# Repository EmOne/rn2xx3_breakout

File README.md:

# rn2xx3_breakout

Feel free to make your own PCB.

Or

You can buy it at http://www.emone.co.th/product/rn2xx3-breakout/

#License
MIT License

Copyright (c) 2018 EmOne

Permission is hereby granted, free of charge, to any person obtaining a copy
of this software and associated documentation files (the "Software"), to deal
in the Software without restriction, including without limitation the rights
to use, copy, modify, merge, publish, distribute, sublicense, and/or sell
copies of the Software, and to permit persons to whom the Software is
furnished to do so, subject to the following conditions:

The above copyright notice and this permission notice shall be included in all
copies or substantial portions of the Software.

THE SOFTWARE IS PROVIDED "AS IS", WITHOUT WARRANTY OF ANY KIND, EXPRESS OR
IMPLIED, INCLUDING BUT NOT LIMITED TO THE WARRANTIES OF MERCHANTABILITY,
FITNESS FOR A PARTICULAR PURPOSE AND NONINFRINGEMENT. IN NO EVENT SHALL THE
AUTHORS OR COPYRIGHT HOLDERS BE LIABLE FOR ANY CLAIM, DAMAGES OR OTHER
LIABILITY, WHETHER IN AN ACTION OF CONTRACT, TORT OR OTHERWISE, ARISING FROM,
OUT OF OR IN CONNECTION WITH THE SOFTWARE OR THE USE OR OTHER DEALINGS IN THE
SOFTWARE.

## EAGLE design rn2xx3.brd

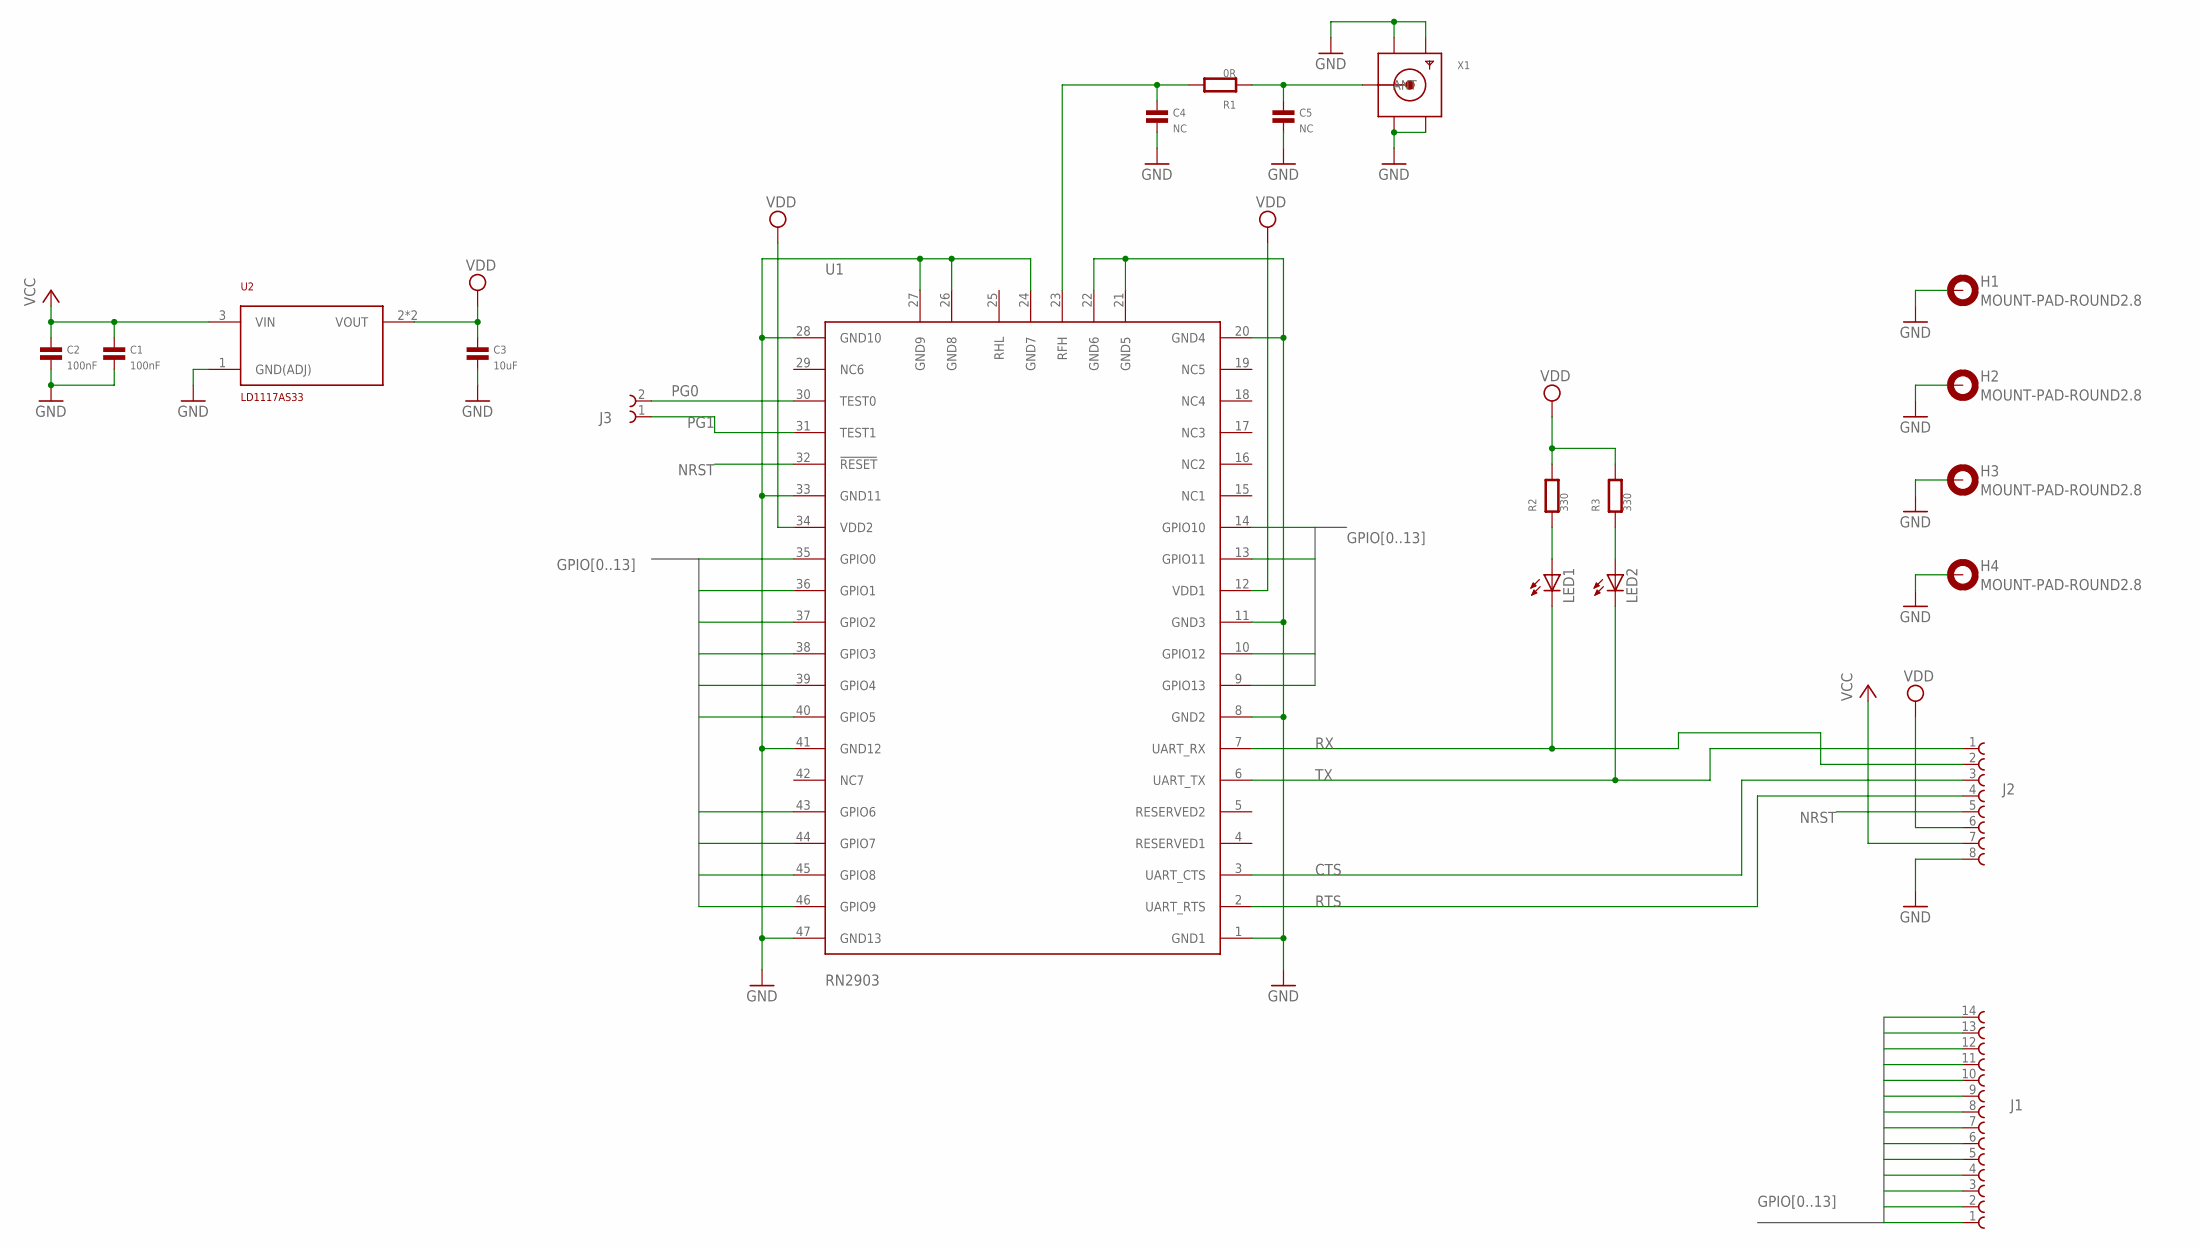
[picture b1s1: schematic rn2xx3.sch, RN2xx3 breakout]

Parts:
C1, C2: 100nF; 0603
C3: 10uF; 0603
C4, C5: NC; 0402
H1, H2, H3, H4: MOUNT-PAD-ROUND2.8; 2,8-PAD
J1: 61301411121
J2: 61300811021
J3: 61300211121
LED1, LED2: LED0603; 0603-LED
R1: 0R; 0402
R2, R3: 330; 0603
U1: RN2903; RN2483/RN2903
U2: LD1117AS33; SOT-223
X1: SMACONNECTOR_EDGE_UFL; SMA_EDGELAUNCH_UFL

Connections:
CTS: J2.3, U1.3 (UART_CTS)
GND: C1.2, C2.2, C3.2, C4.2, C5.2, H1.B2,8, H2.B2,8, H3.B2,8, H4.B2,8, J2.8, U1.1 (GND1), U1.8 (GND2), U1.11 (GND3), U1.20 (GND4), U1.21 (GND5), U1.22 (GND6), U1.24 (GND7), U1.26 (GND8), U1.27 (GND9), U1.28 (GND10), U1.33 (GND11), U1.41 (GND12), U1.47 (GND13), U2.1 (GND(ADJ)), X1.GND@1 (GND1), X1.GND@2 (GND2), X1.GND@3 (GND3), X1.GND@4 (GND4)
GPIO0: J1.1 (14), U1.35 (GPIO0)
GPIO1: J1.2 (13), U1.36 (GPIO1)
GPIO2: J1.3 (12), U1.37 (GPIO2)
GPIO3: J1.4 (11), U1.38 (GPIO3)
GPIO4: J1.5 (10), U1.39 (GPIO4)
GPIO5: J1.6 (9), U1.40 (GPIO5)
GPIO6: J1.7 (8), U1.43 (GPIO6)
GPIO7: J1.8 (7), U1.44 (GPIO7)
GPIO8: J1.9 (6), U1.45 (GPIO8)
GPIO9: J1.10 (5), U1.46 (GPIO9)
GPIO10: J1.11 (4), U1.14 (GPIO10)
GPIO11: J1.12 (3), U1.13 (GPIO11)
GPIO12: J1.13 (2), U1.10 (GPIO12)
GPIO13: J1.14 (1), U1.9 (GPIO13)
unnamed: C4.1, R1.2, U1.23 (RFH)
unnamed: C5.1, R1.1, X1.P (ANT)
unnamed: LED1.A, R2.1
unnamed: LED2.A, R3.1
NRST: J2.5, U1.32 (!RESET)
PG0: J3.2, U1.30 (TEST0)
PG1: J3.1, U1.31 (TEST1)
RTS: J2.4, U1.2 (UART_RTS)
RX: J2.2, LED1.C, U1.7 (UART_RX)
TX: J2.1, LED2.C, U1.6 (UART_TX)
VCC: C1.1, C2.1, J2.7, U2.3 (VIN)
VDD: C3.1, J2.6, R2.2, R3.2, U1.12 (VDD1), U1.34 (VDD2), U2.2 (VOUT), U2.4 (VOUT)

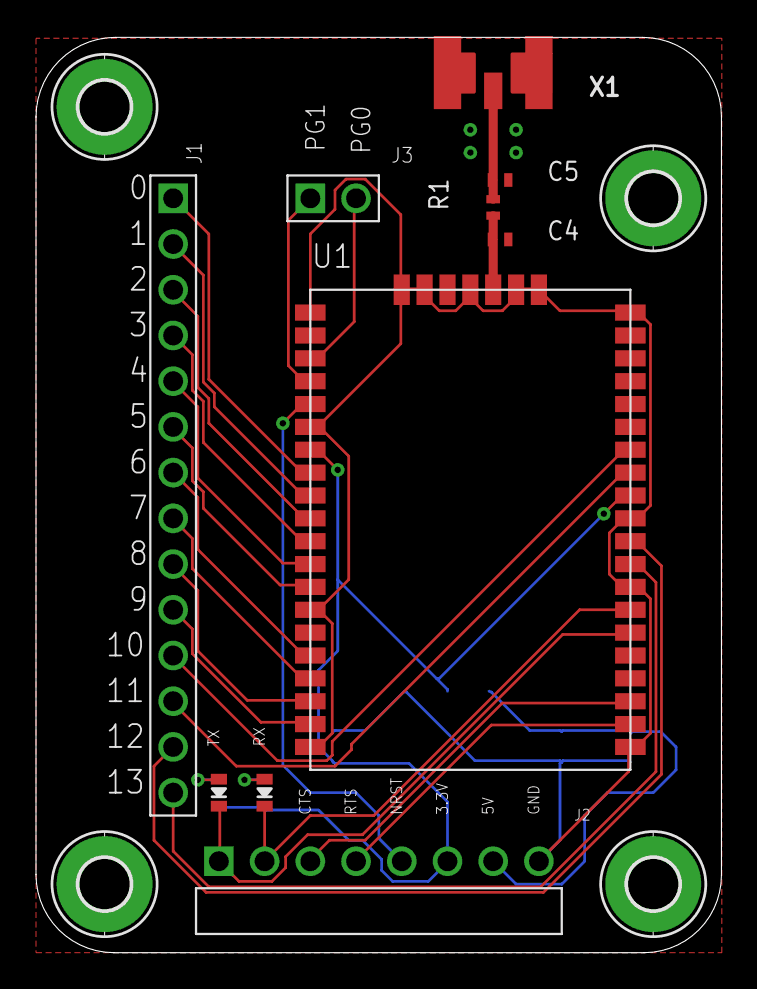
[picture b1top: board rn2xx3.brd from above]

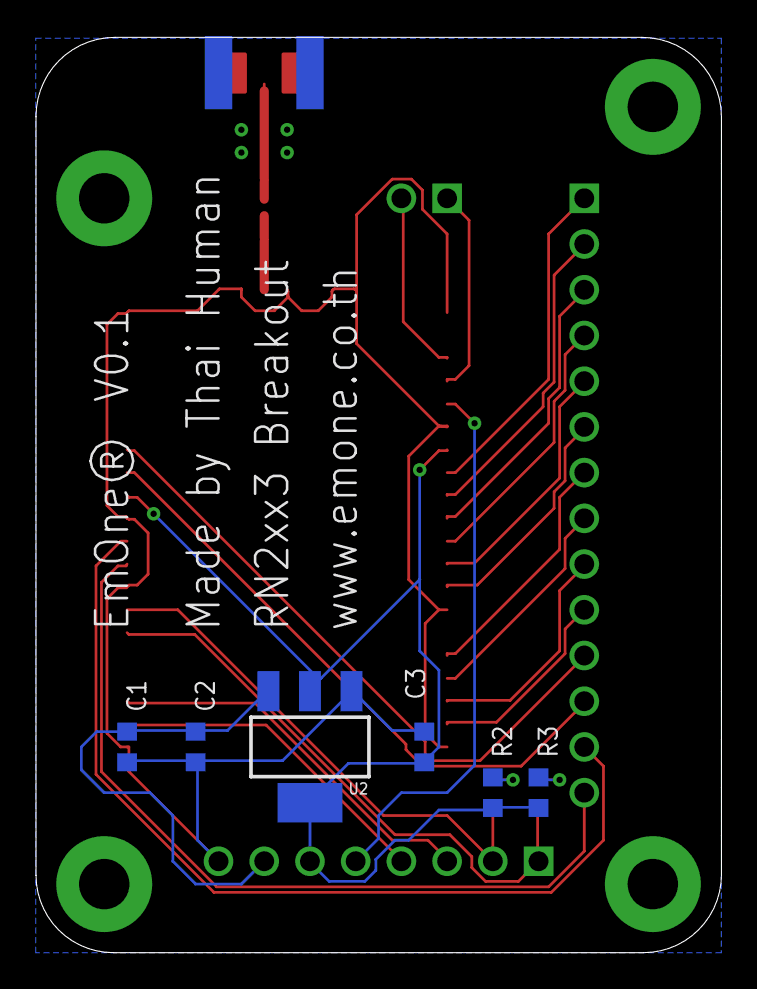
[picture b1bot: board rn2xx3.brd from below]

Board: 2 copper layers, 38.1 x 50.9 mm, 21 parts (6 on the bottom side), 28 nets.

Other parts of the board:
DRILEGEND: DRILEGEND

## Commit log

2018-07-07 First commit.
2018-07-07 Update gerber folder.

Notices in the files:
parts and their libraries:
Wurth_Elektronik_Electromechanic_Board_t: Copyright: Würth Elektronik
sclora: License : GNU General Public License version 2 (see bottom)
sclora: LICENSE: Copyright 2018 @ EmOne
